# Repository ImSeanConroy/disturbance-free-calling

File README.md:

# Disturbance Free Calling

**Minimising disturbances to enable productive remote work** - In today's remote work environment, unintentional interruptions can disrupt productivity and communication. This project aims to solve that challenge by creating an IoT-powered availability indicator that minimizes disturbances during critical work activities such as calls and meetings.

This is **version 2.0**, building on the foundations of the [original version](https://www.linkedin.com/feed/update/urn:li:activity:6930081862153342977) developed in 2020. The initial solution utilized an **ESP32 microcontroller based development board** to poll the **Webex API** and display availability using an **LED strip**.While effective, it had room for improvement in **performance, reliability, and design** — which are now addressed in this upgraded version.

## Table of Contents

- [Monorepo Structure](#monorepo-structure)
- [Features and Development Roadmap](#features-and-development-roadmap)
    - [Current Features](#current-features)
    - [Upcoming Features](#upcoming-features)
- [Architecture Diagram](#architecture-diagram)
- [Getting Started](#getting-started)
    - [1. Clone the Repository](#1-clone-the-repository)
    - [2. Hardware Setup](#2-hardware-setup)
    - [3. AWS Infrastructure Setup](#3-aws-infrastructure-setup)
    - [4. Firmware \& Device Setup](#4-firmware--device-setup)
    - [5. Configure Webex Webhook](#5-configure-webex-webhook)
- [Hardware Requirements](#hardware-requirements)
- [Contributing](#contributing)
- [License](#license)
- [Support](#support)
- [Acknowledgments](#acknowledgments)

## Monorepo Structure

This project uses a monorepo that includes:

- **Hardware** – KiCad PCB files for custom boards
- **Firmware** – ESP32 firmware to drive the LED indicator
- **AWS Infrastructure** – Terraform setup for API Gateway, Lambda, and IoT Core
- **Backend** – Node.js Lambda functions to handle Webex webhook data

## Features and Development Roadmap

This project is a work in progress, the following outlines the current features and planned improvements:

### Current Features

- **Terraform Provisioning** - Automates the setup and deployment of necessary cloud infrastructure.
- **Webhook Integration** - Allows seamless communication between the IoT device and external services.

### Upcoming Features

- **Custom PCB** - Designed specifically to support the IoT-driven indicator system.
- **Custom ESP32 Integration** - Incorporate the newly developed custom ESP32 board into the system architecture.
- **Web UI dashboard** - A web interface that allows users to override availability status manually.

## Architecture Diagram

Below is a high-level overview of how the architecture operates:

**1. Webex Webhook → API Gateway** - A Webex webhook sends a request to an AWS API Gateway endpoint when a user’s availability status changes.

**2. Lambda Function → AWS IoT** - AWS API Gateway triggers an AWS Lambda function, which processes the Webex data and publishes the updated availability status to an AWS IoT Core MQTT topic.

**3. Device Subscribes → Updates LED** - The device subscribes to the AWS IoT topic and receives status updates, updatings the LED indicator accordingly.
 
> **Note**: A polling-based firmware version is available for setups that cannot use Webex webhooks. This version periodically queries the Webex API for status updates.

## Getting Started

Before getting started, ensure you have the following installed:

| Tool        | Purpose                           | Link                                                               |
| ----------- | --------------------------------- | ------------------------------------------------------------------ |
| Node.js     | Backend scripts & Lambda bundling | [Download](https://nodejs.org/)                                    |
| npm         | Node.js package manager           | [Download](https://www.npmjs.com/)                                 |
| Terraform   | Infrastructure provisioning       | [Install Guide](https://developer.hashicorp.com/terraform/install) |
| AWS CLI     | AWS access & configuration        | [AWS CLI](https://aws.amazon.com/cli/)                             |
| Arduino IDE | Firmware upload to ESP32          | [Arduino IDE](https://www.arduino.cc/en/software)                  |
| KiCad       | Open/edit PCB files               | [KiCad](https://www.kicad.org/)                                    |

### 1. Clone the Repository

First, clone the repository to access the firmware, backend, and PCB files:

```bash
git clone https://github.com/ImSeanConroy/disturbance-free-calling.git
cd disturbance-free-calling
```

### 2. Hardware Setup

1. **Open the Project** - Open the `PCB/disturbance-free-calling.kicad_pro` file in KiCad to view the project.
2. **Review the Design** - Inspect the schematic and PCB layout to ensure it meets your needs.
3. **Customize or Export** - Make any modifications and export the Gerber files for fabrication.
4. **Order the PCB** - Submit the Gerber files to your preferred PCB manufacturer (e.g. [JLCPCB](https://jlcpcb.com/capabilities/pcb-capabilities)).
5. **Get the Components** - Purchase the components from the BOM and a compatible board.
6. **Assemble the Hardware** - Solder the components and assemble the board.

### 3. AWS Infrastructure Setup

1. **Zip AWS Lambda Function.**
```bash
cd Backend && npm run install && npm run zip && cd ..
```

2. **Configure Terraform Environment Variables.**
```bash
export AWS_ACCESS_KEY_ID=<your-access-key>
export AWS_SECRET_ACCESS_KEY=<your-secret-key>
export AWS_REGION=<your-region>
```

3. **Deploy AWS Infrastructure**
```bash
terraform init
terraform apply
```

4. **Extract AWS IoT Credentials** - Save these values and add them to your firmware:
```bash
terraform output root_ca_url
terraform output device_certificate
terraform output device_private_key
```

### 4. Firmware & Device Setup

1. **Open Firmware Sketch** - Load Firmware/AwsIotController/AwsIotController.ino in the Arduino IDE.
2. **Configure Device Credentials** - Add Wi-Fi SSID/password and paste the AWS IoT credentials into the appropriate constants.
3. **Upload to Device Firmware** - Compile and upload the sketch to the ESP32 using Arduino IDE. Test connectivity.

### 5. Configure Webex Webhook

> TODO: Add step-by-step instructions for setting up the Webex webhook and linking it to the API Gateway endpoint.

## Hardware Requirements

The following are the required components to build the 2x6 LED Matrix:

| Quantity | Component | Description | Source |
| - | - | - | - |
| 10 | WS2812B-V5 | Individually addressable RGB SMD LEDs | [TME](https://www.tme.eu/gb/details/ws2812b-v5/smd-colour-leds/worldsemi/) |
| 1 | Seeed XIAO ESP32C3 | Microcontroller board | [PiHut](https://thepihut.com/products/seeed-xiao-esp32c3?variant=53975115661697) |
| 1 | USB-A to USB-C Cable | For power and programming | [PiHut](https://thepihut.com/products/usb-a-to-usb-c-cable-1m?variant=42520360779971) |

## Contributing

Contributions are welcome. Please open an issue or submit a pull request for any enhancements or bug fixes.

## License

This project is Distributed under the MIT License - see the [LICENSE](LICENSE) file for information.

## Support

If you are having problems, please let me know by [raising a new issue](https://github.com/ImSeanConroy/disturbance-free-calling/issues/new/choose).

## Acknowledgments

This project was made possible thanks to the following resources:

- [AWS re:Post](https://repost.aws/questions/QUxlg-arOrTcaxFAdNEj7hqA/lambda-publish-a-mqtt-message-to-iot-core-inside-a-lambda-function-with-node-and-sdk-3) - Publish a MQTT Message to IOT Core inside a Lambda function with Node and SDK 3
- [AWS Samples](https://github.com/aws-samples/aws-iot-esp32-arduino-examples) - Several Arduino examples for AWS IoT projects using ESP32.

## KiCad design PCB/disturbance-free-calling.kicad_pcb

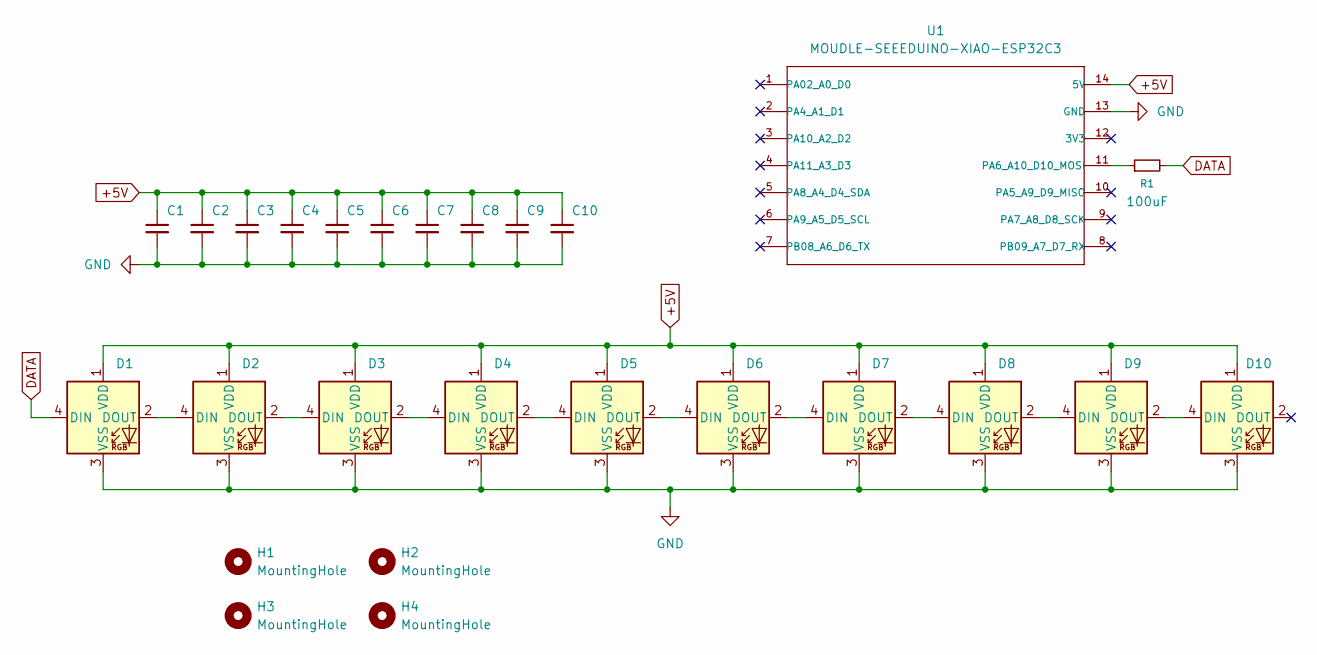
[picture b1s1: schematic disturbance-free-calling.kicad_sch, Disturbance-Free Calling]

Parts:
C1, C2, C3, C4, C5, C6, C7, C8, C9, C10: 100nF; C_0805_2012Metric
D1, D2, D3, D4, D5, D6, D7, D8, D9, D10: WS2812B; LED_WS2812B_PLCC4_5.0x5.0mm_P3.2mm
H1, H2, H3, H4: MountingHole; MountingHole_2.2mm_M2_Pad
R1: 100uF; R_0805_2012Metric
U1: MOUDLE-SEEEDUINO-XIAO-ESP32C3; MOUDLE14P-SMD-2.54-21X17.8MM

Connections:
+5V: C1.1, C2.1, C3.1, C4.1, C5.1, C6.1, C7.1, C8.1, C9.1, C10.1, D1.1 (VDD), D2.1 (VDD), D3.1 (VDD), D4.1 (VDD), D5.1 (VDD), D6.1 (VDD), D7.1 (VDD), D8.1 (VDD), D9.1 (VDD), D10.1 (VDD), U1.14 (5V)
DATA: D1.4 (DIN), R1.2
GND: C1.2, C2.2, C3.2, C4.2, C5.2, C6.2, C7.2, C8.2, C9.2, C10.2, D1.3 (VSS), D2.3 (VSS), D3.3 (VSS), D4.3 (VSS), D5.3 (VSS), D6.3 (VSS), D7.3 (VSS), D8.3 (VSS), D9.3 (VSS), D10.3 (VSS), U1.13 (GND)
unnamed: D1.2 (DOUT), D2.4 (DIN)
unnamed: D2.2 (DOUT), D3.4 (DIN)
unnamed: D3.2 (DOUT), D4.4 (DIN)
unnamed: D4.2 (DOUT), D5.4 (DIN)
unnamed: D5.2 (DOUT), D6.4 (DIN)
unnamed: D6.2 (DOUT), D7.4 (DIN)
unnamed: D7.2 (DOUT), D8.4 (DIN)
unnamed: D8.2 (DOUT), D9.4 (DIN)
unnamed: D9.2 (DOUT), D10.4 (DIN)
unnamed: R1.1, U1.11 (PA6_A10_D10_MOSI)

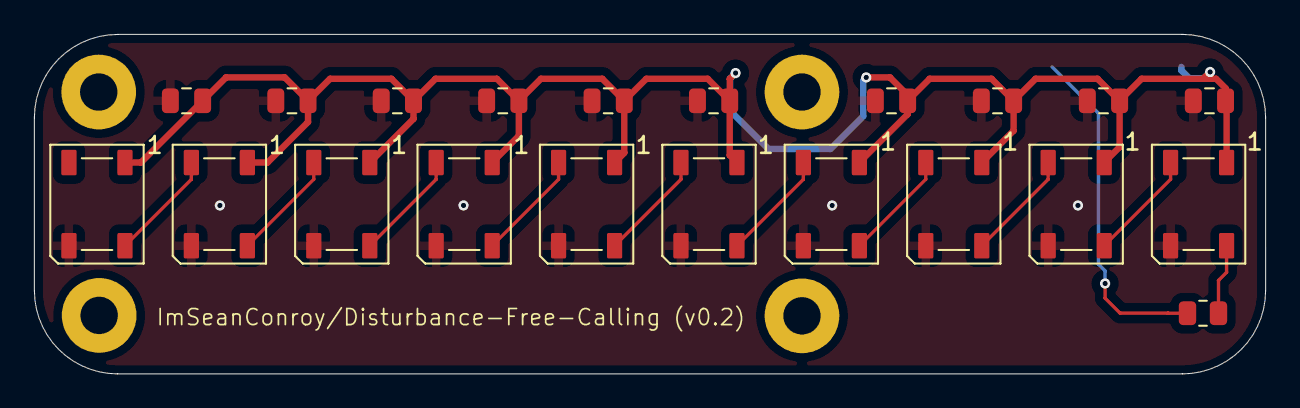
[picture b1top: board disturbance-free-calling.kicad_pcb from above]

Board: 2 copper layers, 72.5 x 20.0 mm, 26 parts (1 on the bottom side), 13 nets.

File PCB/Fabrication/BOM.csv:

Designator,Quantity,JLPCB Part #,Footprint
"C2,C7,C3,C9,C8,C1,C5,C6,C4,C10",10,C_0805_2012Metric,100nF
"D4,D1,D2,D3,D7,D8,D5,D9,D6,D10",10,LED_WS2812B_PLCC4_5.0x5.0mm_P3.2mm,WS2812B
R1,1,R_0805_2012Metric,100uF
U1,1,MOUDLE14P-SMD-2.54-21X17.8MM,MOUDLE-SEEEDUINO-XIAO-ESP32C3

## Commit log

2024-11-24 Add aws iot cloud terraform configuration and arduino firmware to recieve messages
2024-11-25 Implement aws api gateway and lambda
2025-01-16 Add work in progress case
2025-02-09 Create initial pcb using seeed xaio esp32c3
2025-02-09 Fix aws lambda permissions issue
2025-02-11 Create webex polling firmware alternative
2025-02-20 Update aws configuration to use s3
2025-02-23 Create case for led strip version
2025-05-07 Refactor terraform
2025-06-23 Update firmware
2025-07-08 Convert to use ground plane
2025-07-16 Rearrange layout
2025-07-20 Add mounting holes
